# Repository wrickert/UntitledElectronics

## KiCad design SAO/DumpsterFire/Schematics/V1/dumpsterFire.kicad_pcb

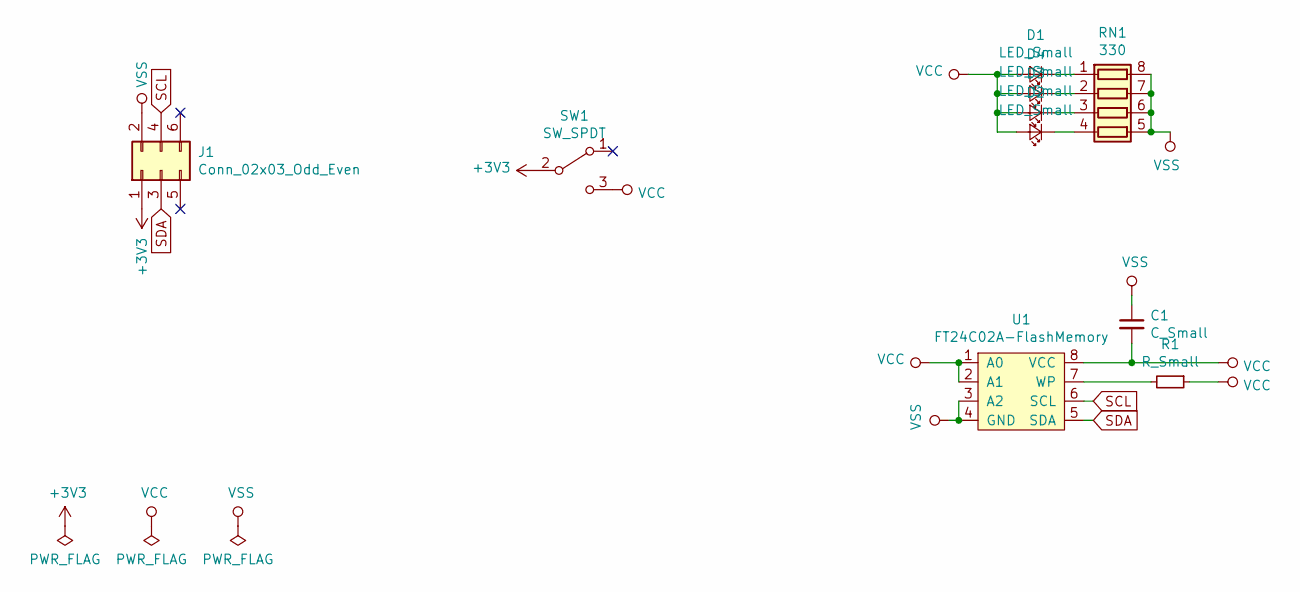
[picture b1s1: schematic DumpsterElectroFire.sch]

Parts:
C1: C_Small; C_0805_2012Metric
D1, D2, D3, D4: LED_Small; LED_0603_1608Metric
J1: Conn_02x03_Odd_Even; PinHeader_2x03_P2.54mm_Vertical_SMD
R1: R_Small; R_0805_2012Metric
RN1: 330; R_Array_Convex_4x0603
SW1: SW_SPDT; SK-3296S_switch
U1: FT24C02A-FlashMemory; SOP-8_3.9x4.9mm_P1.27mm

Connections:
+3V3: J1.1, SW1.2 (B)
unnamed: D1.1 (K), RN1.1 (R1.1)
unnamed: D2.1 (K), RN1.4 (R4.1)
unnamed: D3.1 (K), RN1.3 (R3.1)
unnamed: D4.1 (K), RN1.2 (R2.1)
unnamed: R1.2, U1.7 (WP)
SCL: J1.4, U1.6 (SCL)
SDA: J1.3, U1.5 (SDA)
VCC: C1.2, D1.2 (A), D2.2 (A), D3.2 (A), D4.2 (A), R1.1, SW1.3 (C), U1.1 (A0), U1.2 (A1), U1.8 (VCC)
VSS: C1.1, J1.2, RN1.5 (R4.2), RN1.6 (R3.2), RN1.7 (R2.2), RN1.8 (R1.2), U1.3 (A2), U1.4 (GND)

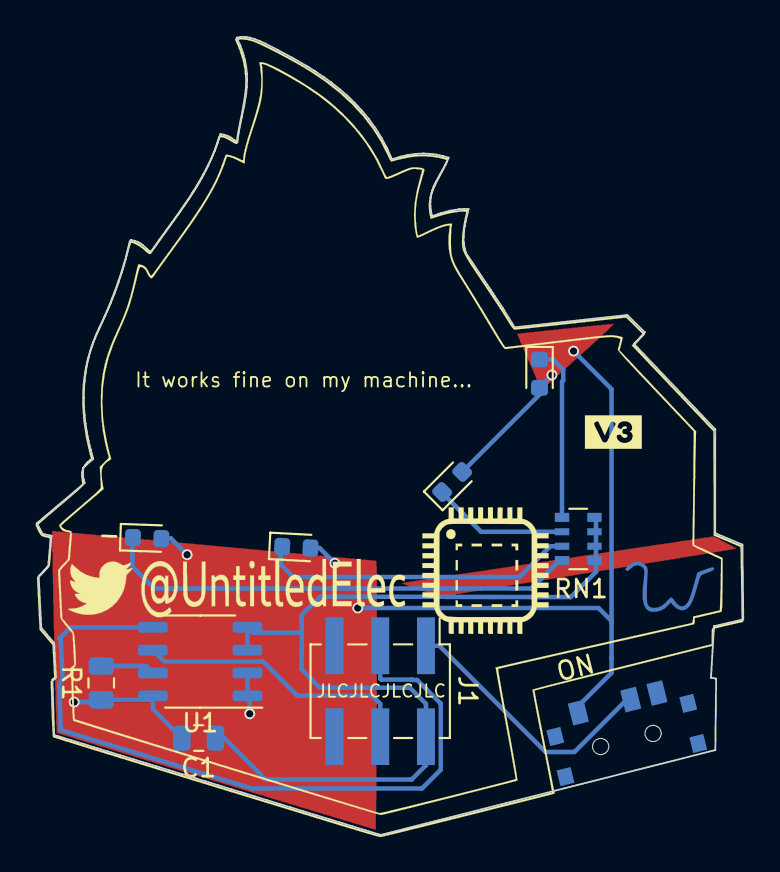
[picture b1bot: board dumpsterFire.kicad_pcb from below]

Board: 2 copper layers, 39.2 x 44.3 mm, 15 parts (14 on the bottom side), 10 nets.

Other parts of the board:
Ref**: Val**; dumpsterFireMiddle
Ref**#2: Val**; W
Ref**#3: Val**; TwitterSmaller
Ref**#4: Val**; JustChip
svg2mod: G***; svg2mod

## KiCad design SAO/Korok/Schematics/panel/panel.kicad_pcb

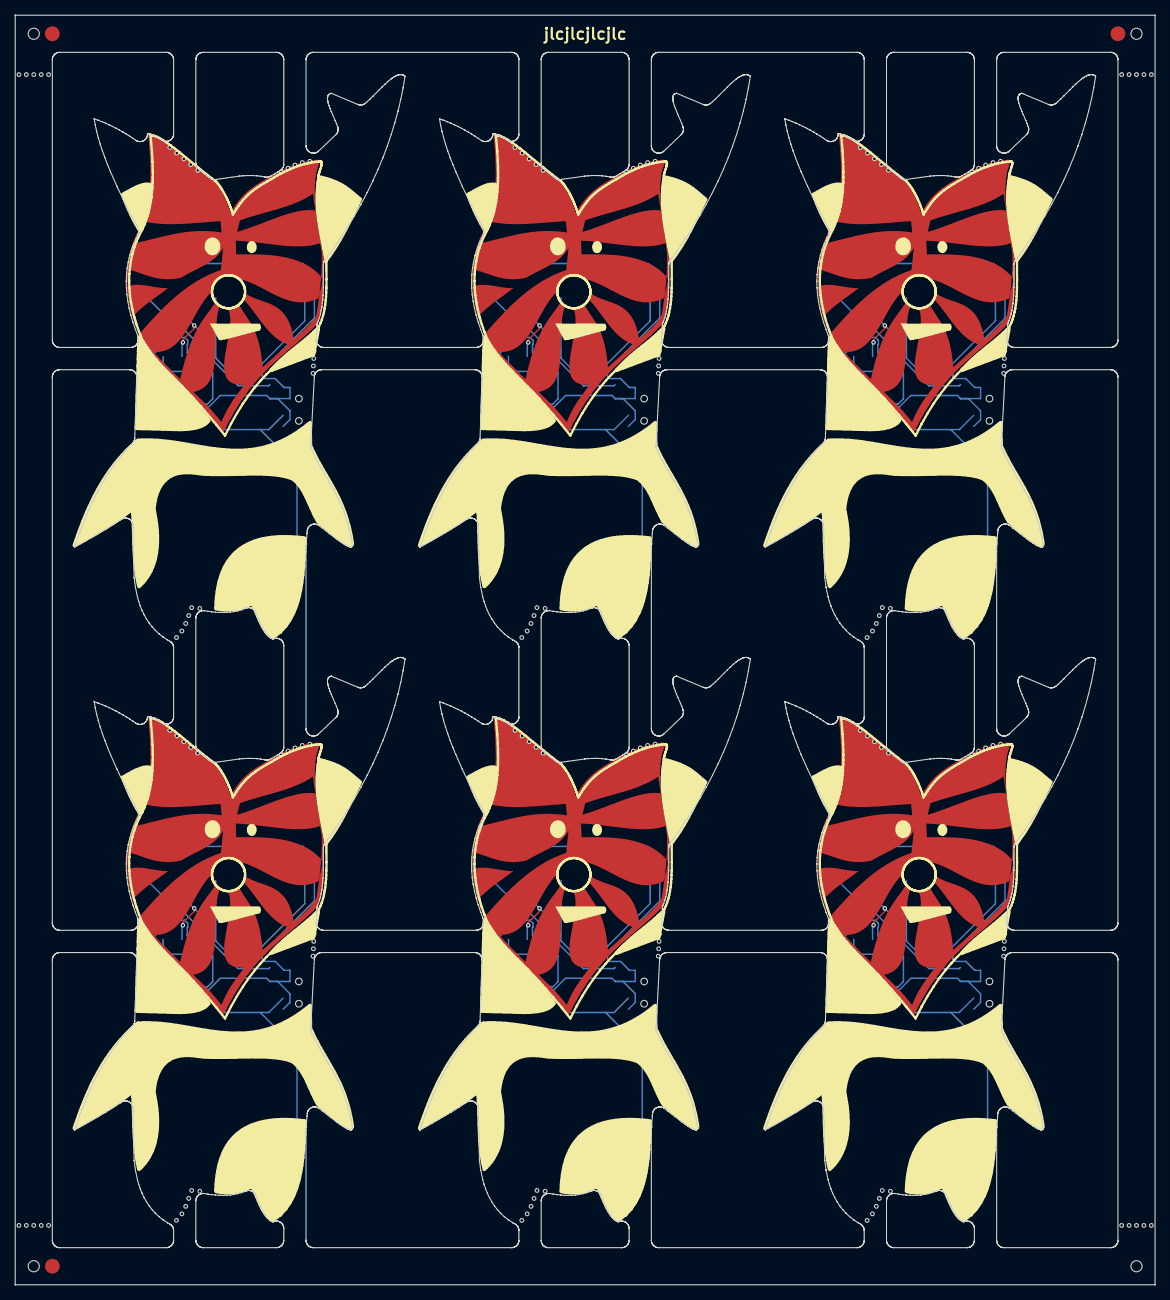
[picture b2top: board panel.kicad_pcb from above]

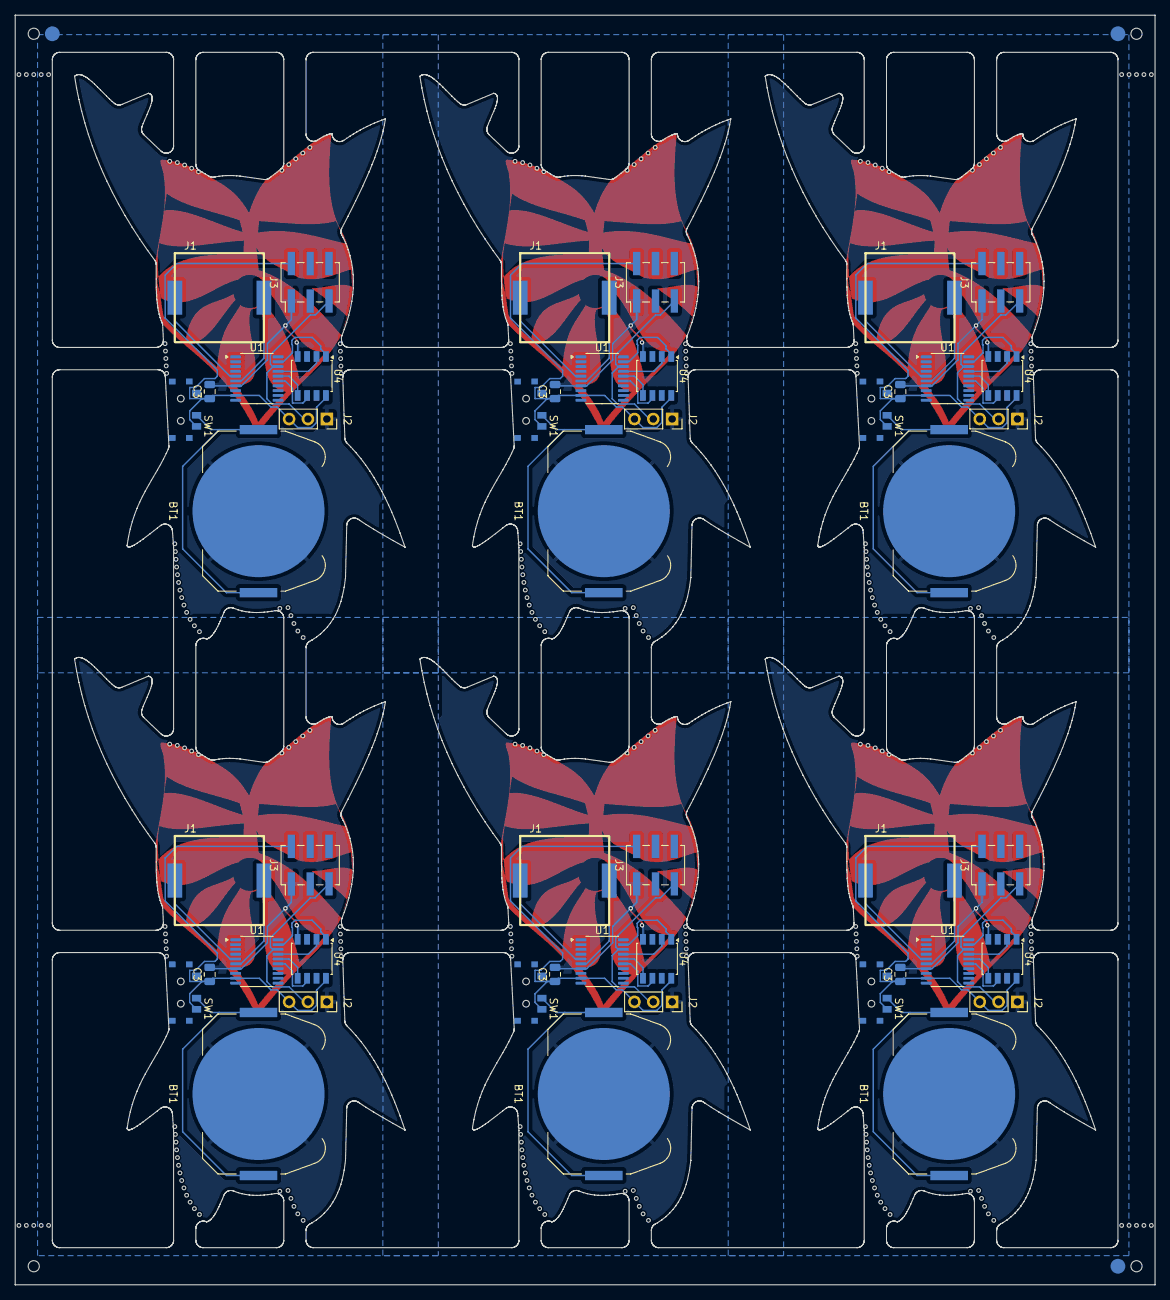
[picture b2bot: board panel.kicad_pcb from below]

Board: 2 copper layers, 153.6 x 171.1 mm, 312 parts (51 on the bottom side), 60 nets.

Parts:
BT1, BT1#2, BT1#3, BT1#4, BT1#5, BT1#6: Battery_Cell; BatteryHolder_Keystone_3034_1x20mm
C3, C3#2, C3#3, C3#4, C3#5, C3#6: 100n; C_0805_2012Metric
J1, J1#2, J1#3, J1#4, J1#5, J1#6: Speaker; Fuet-1230
J2, J2#2, J2#3, J2#4, J2#5, J2#6: Debug; PinSocket_1x03_P2.54mm_Vertical
J3, J3#2, J3#3, J3#4, J3#5, J3#6: Conn_02x03_Odd_Even; PinHeader_2x03_P2.54mm_Vertical_SMD
KiKit_FID_B_1, KiKit_FID_B_2, KiKit_FID_B_3: Fiducial
KiKit_FID_T_1, KiKit_FID_T_2, KiKit_FID_T_3: Fiducial
KiKit_MB_1_1, KiKit_MB_1_2, KiKit_MB_1_3, KiKit_MB_1_4, KiKit_MB_1_5, KiKit_MB_2_1, KiKit_MB_2_2, KiKit_MB_2_3, KiKit_MB_2_4, KiKit_MB_2_5, KiKit_MB_3_1, KiKit_MB_3_2, KiKit_MB_3_3, KiKit_MB_3_4, KiKit_MB_3_5, KiKit_MB_4_1, KiKit_MB_4_2, KiKit_MB_4_3, KiKit_MB_4_4, KiKit_MB_4_5, KiKit_MB_5_1, KiKit_MB_5_2, KiKit_MB_5_3, KiKit_MB_5_4, KiKit_MB_5_5, KiKit_MB_5_6, KiKit_MB_6_1, KiKit_MB_6_2, KiKit_MB_6_3, KiKit_MB_6_4, KiKit_MB_6_5, KiKit_MB_6_6, KiKit_MB_6_7, KiKit_MB_6_8, KiKit_MB_6_9, KiKit_MB_6_10, KiKit_MB_6_11, KiKit_MB_6_12, KiKit_MB_6_13, KiKit_MB_7_1, KiKit_MB_7_2, KiKit_MB_7_3, KiKit_MB_7_4, KiKit_MB_7_5, KiKit_MB_8_1, KiKit_MB_8_2, KiKit_MB_8_3, KiKit_MB_8_4, KiKit_MB_8_5, KiKit_MB_9_1, KiKit_MB_9_2, KiKit_MB_9_3, KiKit_MB_9_4, KiKit_MB_9_5, KiKit_MB_10_1, KiKit_MB_10_2, KiKit_MB_10_3, KiKit_MB_10_4, KiKit_MB_10_5, KiKit_MB_11_1, KiKit_MB_11_2, KiKit_MB_11_3, KiKit_MB_11_4, KiKit_MB_11_5, KiKit_MB_11_6, KiKit_MB_12_1, KiKit_MB_12_2, KiKit_MB_12_3, KiKit_MB_12_4, KiKit_MB_12_5, KiKit_MB_12_6, KiKit_MB_12_7, KiKit_MB_12_8, KiKit_MB_12_9, KiKit_MB_12_10, KiKit_MB_12_11, KiKit_MB_12_12, KiKit_MB_12_13, KiKit_MB_13_1, KiKit_MB_13_2, KiKit_MB_13_3, KiKit_MB_13_4, KiKit_MB_13_5, KiKit_MB_14_1, KiKit_MB_14_2, KiKit_MB_14_3, KiKit_MB_14_4, KiKit_MB_14_5, KiKit_MB_15_1, KiKit_MB_15_2, KiKit_MB_15_3, KiKit_MB_15_4, KiKit_MB_15_5, KiKit_MB_16_1, KiKit_MB_16_2, KiKit_MB_16_3, KiKit_MB_16_4, KiKit_MB_16_5, KiKit_MB_17_1, KiKit_MB_17_2, KiKit_MB_17_3, KiKit_MB_17_4, KiKit_MB_17_5, KiKit_MB_17_6, KiKit_MB_18_1, KiKit_MB_18_2, KiKit_MB_18_3, KiKit_MB_18_4, KiKit_MB_18_5, KiKit_MB_18_6, KiKit_MB_18_7, KiKit_MB_18_8, KiKit_MB_18_9, KiKit_MB_18_10, KiKit_MB_18_11, KiKit_MB_18_12, KiKit_MB_18_13, KiKit_MB_19_1, KiKit_MB_19_2, KiKit_MB_19_3, KiKit_MB_19_4, KiKit_MB_19_5, KiKit_MB_20_1, KiKit_MB_20_2, KiKit_MB_20_3, KiKit_MB_20_4, KiKit_MB_20_5, KiKit_MB_21_1, KiKit_MB_21_2, KiKit_MB_21_3, KiKit_MB_21_4, KiKit_MB_21_5, KiKit_MB_22_1, KiKit_MB_22_2, KiKit_MB_22_3, KiKit_MB_22_4, KiKit_MB_22_5, KiKit_MB_23_1, KiKit_MB_23_2, KiKit_MB_23_3, KiKit_MB_23_4, KiKit_MB_23_5, KiKit_MB_23_6, KiKit_MB_24_1, KiKit_MB_24_2, KiKit_MB_24_3, KiKit_MB_24_4, KiKit_MB_24_5, KiKit_MB_24_6, KiKit_MB_24_7, KiKit_MB_24_8, KiKit_MB_24_9, KiKit_MB_24_10, KiKit_MB_24_11, KiKit_MB_24_12, KiKit_MB_24_13, KiKit_MB_25_1, KiKit_MB_25_2, KiKit_MB_25_3, KiKit_MB_25_4, KiKit_MB_25_5, KiKit_MB_26_1, KiKit_MB_26_2, KiKit_MB_26_3, KiKit_MB_26_4, KiKit_MB_26_5, KiKit_MB_27_1, KiKit_MB_27_2, KiKit_MB_27_3, KiKit_MB_27_4, KiKit_MB_27_5, KiKit_MB_28_1, KiKit_MB_28_2, KiKit_MB_28_3, KiKit_MB_28_4, KiKit_MB_28_5, KiKit_MB_29_1, KiKit_MB_29_2, KiKit_MB_29_3, KiKit_MB_29_4, KiKit_MB_29_5, KiKit_MB_29_6, KiKit_MB_30_1, KiKit_MB_30_2, KiKit_MB_30_3, KiKit_MB_30_4, KiKit_MB_30_5, KiKit_MB_30_6, KiKit_MB_30_7, KiKit_MB_30_8, KiKit_MB_30_9, KiKit_MB_30_10, KiKit_MB_30_11, KiKit_MB_30_12, KiKit_MB_30_13, KiKit_MB_31_1, KiKit_MB_31_2, KiKit_MB_31_3, KiKit_MB_31_4, KiKit_MB_31_5, KiKit_MB_32_1, KiKit_MB_32_2, KiKit_MB_32_3, KiKit_MB_32_4, KiKit_MB_32_5, KiKit_MB_33_1, KiKit_MB_33_2, KiKit_MB_33_3, KiKit_MB_33_4, KiKit_MB_33_5, KiKit_MB_34_1, KiKit_MB_34_2, KiKit_MB_34_3, KiKit_MB_34_4, KiKit_MB_34_5, KiKit_MB_35_1, KiKit_MB_35_2, KiKit_MB_35_3, KiKit_MB_35_4, KiKit_MB_35_5, KiKit_MB_35_6, KiKit_MB_36_1, KiKit_MB_36_2, KiKit_MB_36_3, KiKit_MB_36_4, KiKit_MB_36_5, KiKit_MB_36_6, KiKit_MB_36_7, KiKit_MB_36_8, KiKit_MB_36_9, KiKit_MB_36_10, KiKit_MB_36_11, KiKit_MB_36_12, KiKit_MB_36_13, KiKit_MB_37_2, KiKit_MB_37_3, KiKit_MB_37_4, KiKit_MB_37_5, KiKit_MB_37_6, KiKit_MB_38_2, KiKit_MB_38_3, KiKit_MB_38_4, KiKit_MB_38_5, KiKit_MB_38_6, KiKit_MB_39_2, KiKit_MB_39_3, KiKit_MB_39_4, KiKit_MB_39_5, KiKit_MB_39_6, KiKit_MB_40_2, KiKit_MB_40_3, KiKit_MB_40_4, KiKit_MB_40_5, KiKit_MB_40_6: NPTH
KiKit_TO_1, KiKit_TO_2, KiKit_TO_3, KiKit_TO_4: NPTH
SW1, SW1#2, SW1#3, SW1#4, SW1#5, SW1#6: SW_SPDT; SK-3296S_switch
U1, U1#2, U1#3, U1#4, U1#5, U1#6: CH32V006; TSSOP-20_4.4x6.5mm_P0.65mm
U4, U4#2, U4#3, U4#4, U4#5, U4#6: W25Q16JVSS; SSOP-8_3.95x5.21x3.27mm_P1.27mm

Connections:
Board_0-+3V3: C3#5.1, J2#5.3, J3#3.2, SW1#5.1 (A), U1#3.9 (VDD), U4.8 (VCC)
Board_0-GND: BT1#5.2 (-), C3#5.2, J2#5.1, J3#3.1, U1#3.7 (VSS), U4.4 (GND)
Board_0-Net-(BT1-+): BT1#5.1 (+), SW1#5.2 (B)
Board_0-PA1: J1#2.1, U1#3.5 (PA1/T1/T2/OPN0/XI/A1)
Board_0-PA2: J1#2.2, U1#3.6 (PA2/T1/T2/U2TX_/OPP0/XO/A0)
Board_0-PC5: U1#3.15 (PC5/T1C2_/T1/T2/TX_/SCK), U4.6 (CLK)
Board_0-PC6: U1#3.16 (PC6/T1C3_/T1/RX_/MOSI), U4.5 (DI(IO0))
Board_0-PC7: U1#3.17 (PC7/T1C4_/T1/T2/MISO), U4.2 (DO(IO1))
Board_0-PD2: U1#3.19 (PD2/T1/T2/U2TX_/A3), U4.1 (~CS)
Board_0-SWIO: J2#5.2, J3#3.5, U1#3.18 (PD1/SWIO/T1/SCL_/RX_/OPP3)
Board_1-+3V3: C3#4.1, J2#2.3, J3#5.2, SW1#2.1 (A), U1#4.9 (VDD), U4#2.8 (VCC)
Board_1-GND: BT1#6.2 (-), C3#4.2, J2#2.1, J3#5.1, U1#4.7 (VSS), U4#2.4 (GND)
Board_1-Net-(BT1-+): BT1#6.1 (+), SW1#2.2 (B)
Board_1-PA1: J1#4.1, U1#4.5 (PA1/T1/T2/OPN0/XI/A1)
Board_1-PA2: J1#4.2, U1#4.6 (PA2/T1/T2/U2TX_/OPP0/XO/A0)
Board_1-PC5: U1#4.15 (PC5/T1C2_/T1/T2/TX_/SCK), U4#2.6 (CLK)
Board_1-PC6: U1#4.16 (PC6/T1C3_/T1/RX_/MOSI), U4#2.5 (DI(IO0))
Board_1-PC7: U1#4.17 (PC7/T1C4_/T1/T2/MISO), U4#2.2 (DO(IO1))
Board_1-PD2: U1#4.19 (PD2/T1/T2/U2TX_/A3), U4#2.1 (~CS)
Board_1-SWIO: J2#2.2, J3#5.5, U1#4.18 (PD1/SWIO/T1/SCL_/RX_/OPP3)
Board_2-+3V3: C3#6.1, J2.3, J3#4.2, SW1#4.1 (A), U1.9 (VDD), U4#4.8 (VCC)
Board_2-GND: BT1#4.2 (-), C3#6.2, J2.1, J3#4.1, U1.7 (VSS), U4#4.4 (GND)
Board_2-Net-(BT1-+): BT1#4.1 (+), SW1#4.2 (B)
Board_2-PA1: J1#6.1, U1.5 (PA1/T1/T2/OPN0/XI/A1)
Board_2-PA2: J1#6.2, U1.6 (PA2/T1/T2/U2TX_/OPP0/XO/A0)
Board_2-PC5: U1.15 (PC5/T1C2_/T1/T2/TX_/SCK), U4#4.6 (CLK)
Board_2-PC6: U1.16 (PC6/T1C3_/T1/RX_/MOSI), U4#4.5 (DI(IO0))
Board_2-PC7: U1.17 (PC7/T1C4_/T1/T2/MISO), U4#4.2 (DO(IO1))
Board_2-PD2: U1.19 (PD2/T1/T2/U2TX_/A3), U4#4.1 (~CS)
Board_2-SWIO: J2.2, J3#4.5, U1.18 (PD1/SWIO/T1/SCL_/RX_/OPP3)
Board_3-+3V3: C3#3.1, J2#6.3, J3#6.2, SW1#6.1 (A), U1#2.9 (VDD), U4#3.8 (VCC)
Board_3-GND: BT1.2 (-), C3#3.2, J2#6.1, J3#6.1, U1#2.7 (VSS), U4#3.4 (GND)
Board_3-Net-(BT1-+): BT1.1 (+), SW1#6.2 (B)
Board_3-PA1: J1#3.1, U1#2.5 (PA1/T1/T2/OPN0/XI/A1)
Board_3-PA2: J1#3.2, U1#2.6 (PA2/T1/T2/U2TX_/OPP0/XO/A0)
Board_3-PC5: U1#2.15 (PC5/T1C2_/T1/T2/TX_/SCK), U4#3.6 (CLK)
Board_3-PC6: U1#2.16 (PC6/T1C3_/T1/RX_/MOSI), U4#3.5 (DI(IO0))
Board_3-PC7: U1#2.17 (PC7/T1C4_/T1/T2/MISO), U4#3.2 (DO(IO1))
Board_3-PD2: U1#2.19 (PD2/T1/T2/U2TX_/A3), U4#3.1 (~CS)
Board_3-SWIO: J2#6.2, J3#6.5, U1#2.18 (PD1/SWIO/T1/SCL_/RX_/OPP3)
Board_4-+3V3: C3.1, J2#3.3, J3.2, SW1#3.1 (A), U1#6.9 (VDD), U4#5.8 (VCC)
Board_4-GND: BT1#2.2 (-), C3.2, J2#3.1, J3.1, U1#6.7 (VSS), U4#5.4 (GND)
Board_4-Net-(BT1-+): BT1#2.1 (+), SW1#3.2 (B)
Board_4-PA1: J1.1, U1#6.5 (PA1/T1/T2/OPN0/XI/A1)
Board_4-PA2: J1.2, U1#6.6 (PA2/T1/T2/U2TX_/OPP0/XO/A0)
Board_4-PC5: U1#6.15 (PC5/T1C2_/T1/T2/TX_/SCK), U4#5.6 (CLK)
Board_4-PC6: U1#6.16 (PC6/T1C3_/T1/RX_/MOSI), U4#5.5 (DI(IO0))
Board_4-PC7: U1#6.17 (PC7/T1C4_/T1/T2/MISO), U4#5.2 (DO(IO1))
Board_4-PD2: U1#6.19 (PD2/T1/T2/U2TX_/A3), U4#5.1 (~CS)
Board_4-SWIO: J2#3.2, J3.5, U1#6.18 (PD1/SWIO/T1/SCL_/RX_/OPP3)
Board_5-+3V3: C3#2.1, J2#4.3, J3#2.2, SW1.1 (A), U1#5.9 (VDD), U4#6.8 (VCC)
Board_5-GND: BT1#3.2 (-), C3#2.2, J2#4.1, J3#2.1, U1#5.7 (VSS), U4#6.4 (GND)
Board_5-Net-(BT1-+): BT1#3.1 (+), SW1.2 (B)
Board_5-PA1: J1#5.1, U1#5.5 (PA1/T1/T2/OPN0/XI/A1)
Board_5-PA2: J1#5.2, U1#5.6 (PA2/T1/T2/U2TX_/OPP0/XO/A0)
Board_5-PC5: U1#5.15 (PC5/T1C2_/T1/T2/TX_/SCK), U4#6.6 (CLK)
Board_5-PC6: U1#5.16 (PC6/T1C3_/T1/RX_/MOSI), U4#6.5 (DI(IO0))
Board_5-PC7: U1#5.17 (PC7/T1C4_/T1/T2/MISO), U4#6.2 (DO(IO1))
Board_5-PD2: U1#5.19 (PD2/T1/T2/U2TX_/A3), U4#6.1 (~CS)
Board_5-SWIO: J2#4.2, J3#2.5, U1#5.18 (PD1/SWIO/T1/SCL_/RX_/OPP3)

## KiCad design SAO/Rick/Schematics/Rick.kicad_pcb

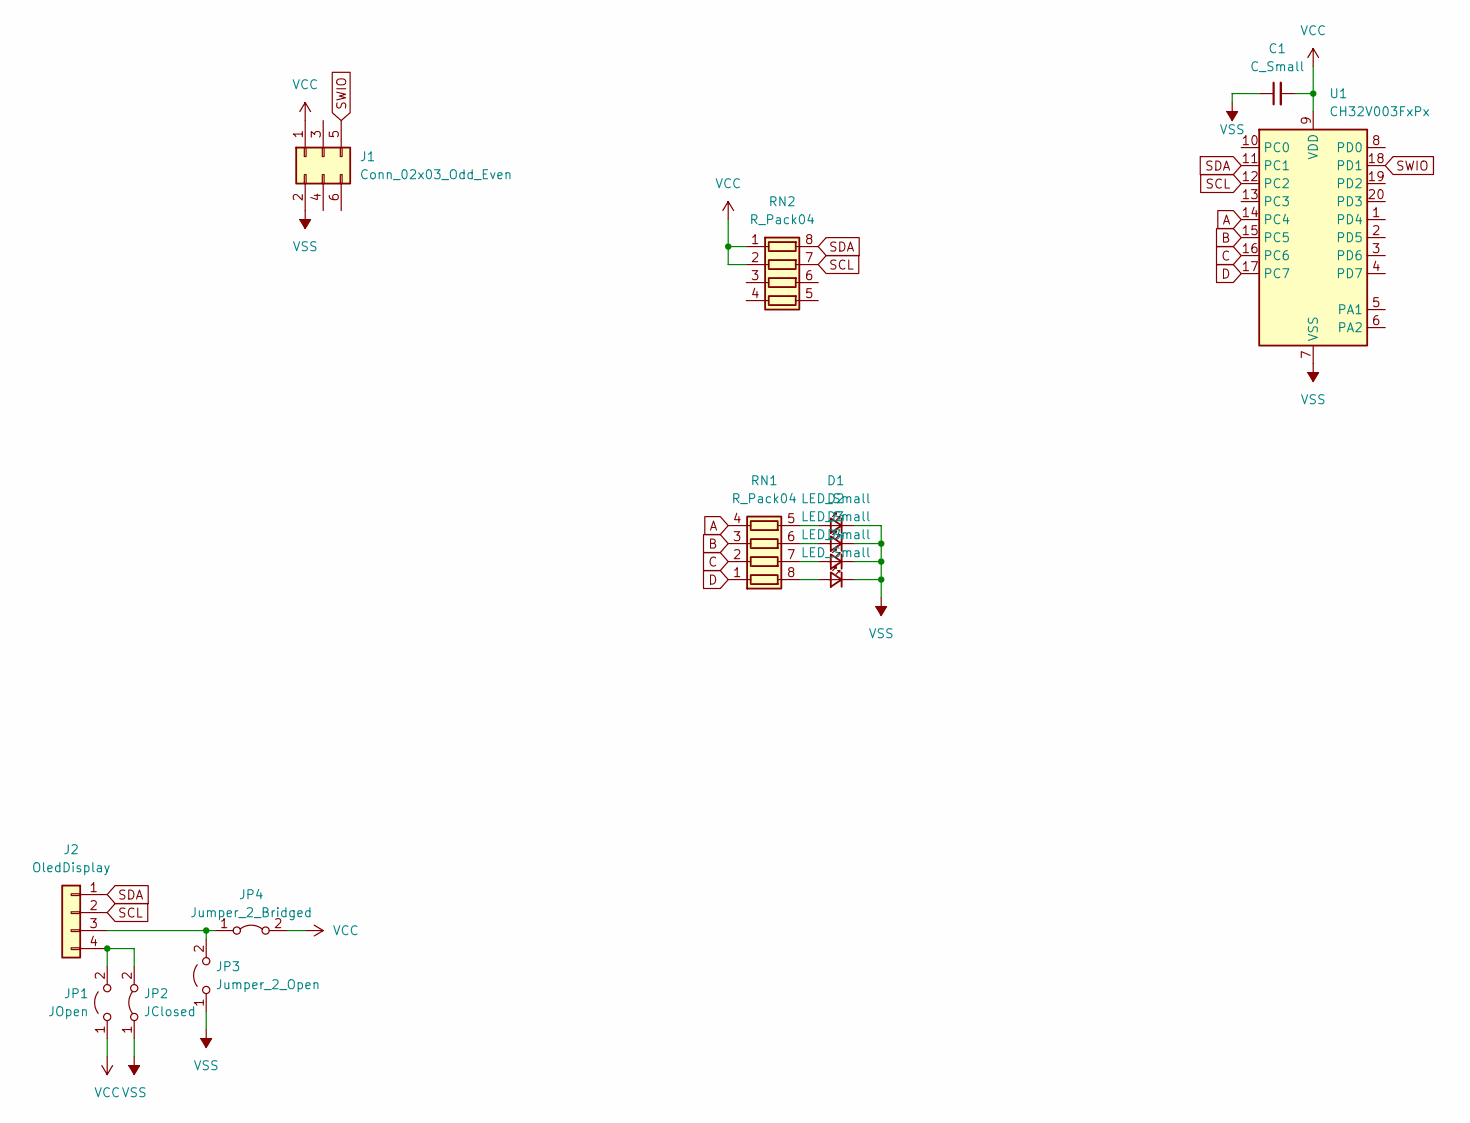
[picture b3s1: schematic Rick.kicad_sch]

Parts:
C1: C_Small; C_0805_2012Metric
D1, D2, D3, D4: LED_Small; 156120VS75000-ReverseCircle
J1: Conn_02x03_Odd_Even; PinHeader_2x03_P2.54mm_Vertical_SMD
J2: OledDisplay; PinHeader_1x04_P2.54mm_Vertical
JP1: JOpen; SolderJumper-2_P1.3mm_Open_TrianglePad1.0x1.5mm
JP2: JClosed; SolderJumper-2_P1.3mm_Bridged_Pad1.0x1.5mm
JP3: Jumper_2_Open; SolderJumper-2_P1.3mm_Open_TrianglePad1.0x1.5mm
JP4: Jumper_2_Bridged; SolderJumper-2_P1.3mm_Bridged_Pad1.0x1.5mm
RN1, RN2: R_Pack04; R_Array_Convex_4x0603
U1: CH32V003FxPx; TSSOP-20_4.4x6.5mm_P0.65mm

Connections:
A: RN1.4 (R4.1), U1.14 (PC4)
B: RN1.3 (R3.1), U1.15 (PC5)
C: RN1.2 (R2.1), U1.16 (PC6)
D: RN1.1 (R1.1), U1.17 (PC7)
unnamed: D1.2 (A), RN1.5 (R4.2)
unnamed: D2.2 (A), RN1.6 (R3.2)
unnamed: D3.2 (A), RN1.7 (R2.2)
unnamed: D4.2 (A), RN1.8 (R1.2)
unnamed: J2.3, JP3.2 (B), JP4.1 (A)
unnamed: J2.4, JP1.2 (B), JP2.2 (B)
SCL: J2.2, RN2.7 (R2.2), U1.12 (PC2)
SDA: J2.1, RN2.8 (R1.2), U1.11 (PC1)
SWIO: J1.5, U1.18 (PD1)
VCC: C1.2, J1.1, JP1.1 (A), JP4.2 (B), RN2.1 (R1.1), RN2.2 (R2.1), U1.9 (VDD)
VSS: C1.1, D1.1 (K), D2.1 (K), D3.1 (K), D4.1 (K), J1.2, JP2.1 (A), JP3.1 (A), U1.7 (VSS)

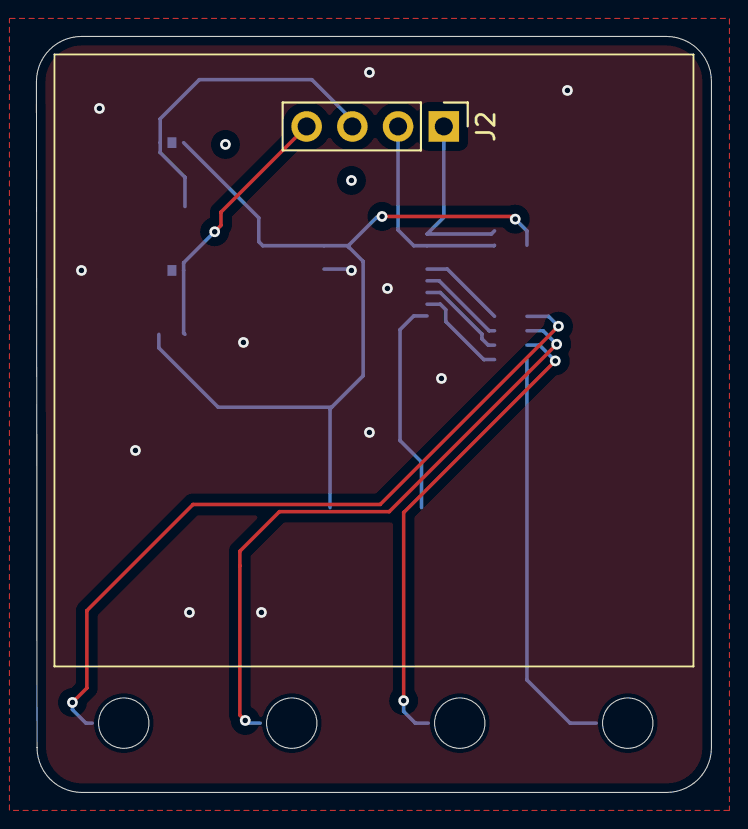
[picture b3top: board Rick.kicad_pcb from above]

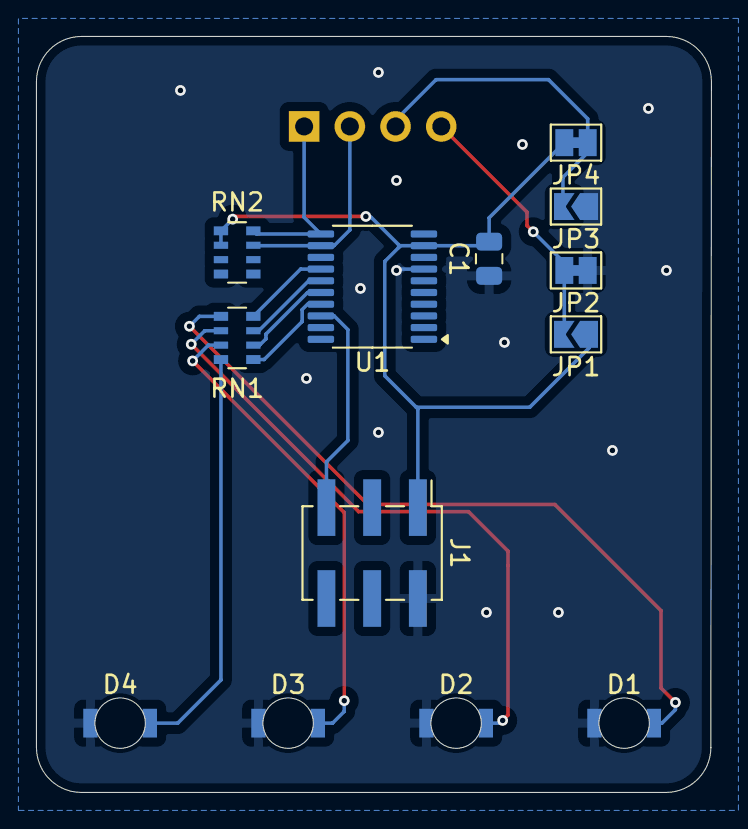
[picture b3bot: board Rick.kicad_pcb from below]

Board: 2 copper layers, 37.5 x 42.0 mm, 14 parts (13 on the bottom side), 15 nets.

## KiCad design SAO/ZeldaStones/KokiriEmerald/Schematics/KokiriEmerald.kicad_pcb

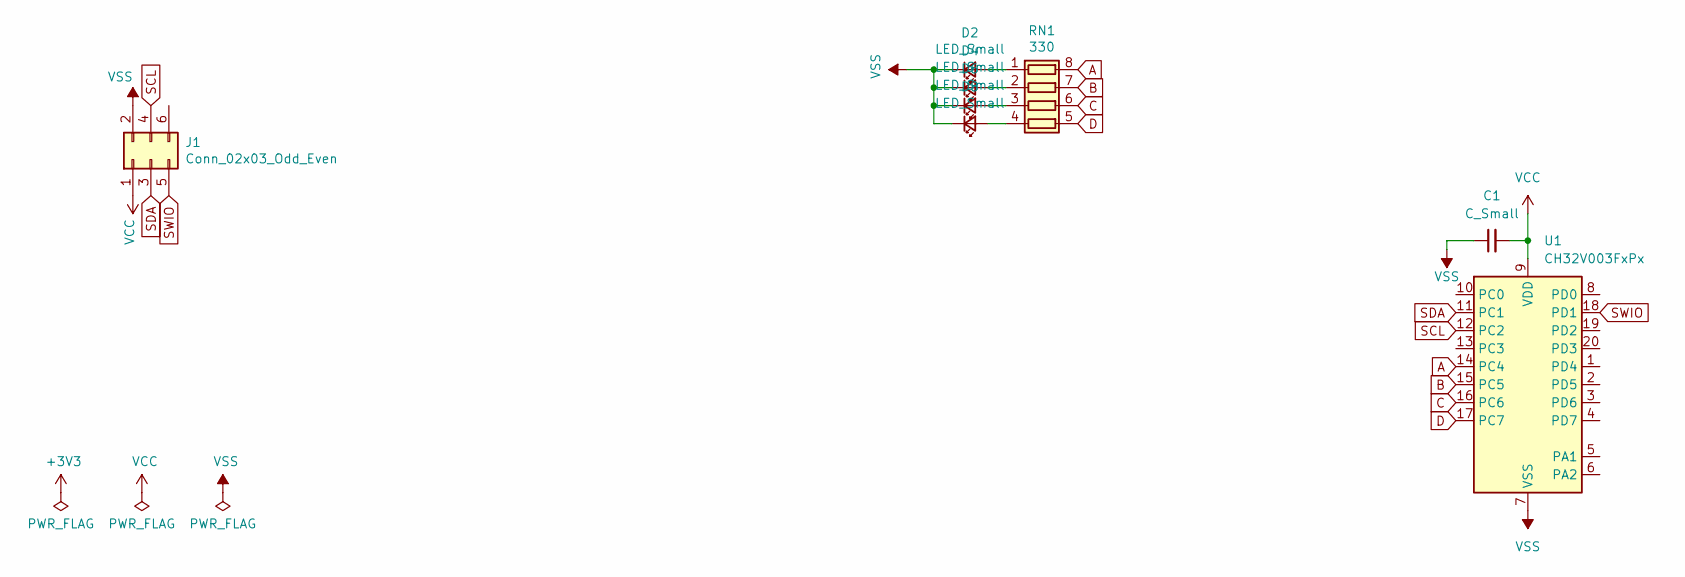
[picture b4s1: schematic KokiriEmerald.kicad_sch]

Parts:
C1: C_Small; C_0805_2012Metric
D2, D4, D6, D8: LED_Small; LED_0603_1608Metric
J1: Conn_02x03_Odd_Even; PinHeader_2x03_P2.54mm_Vertical_SMD
RN1: 330; R_Array_Convex_4x0603
U1: CH32V003FxPx; TSSOP-20_4.4x6.5mm_P0.65mm

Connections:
A: RN1.8 (R1.2), U1.14 (PC4)
B: RN1.7 (R2.2), U1.15 (PC5)
C: RN1.6 (R3.2), U1.16 (PC6)
D: RN1.5 (R4.2), U1.17 (PC7)
unnamed: D2.2 (A), RN1.1 (R1.1)
unnamed: D4.2 (A), RN1.2 (R2.1)
unnamed: D6.2 (A), RN1.3 (R3.1)
unnamed: D8.2 (A), RN1.4 (R4.1)
SCL: J1.4, U1.12 (PC2)
SDA: J1.3, U1.11 (PC1)
SWIO: J1.5, U1.18 (PD1)
VCC: C1.2, J1.1, U1.9 (VDD)
VSS: C1.1, D2.1 (K), D4.1 (K), D6.1 (K), D8.1 (K), J1.2, U1.7 (VSS)

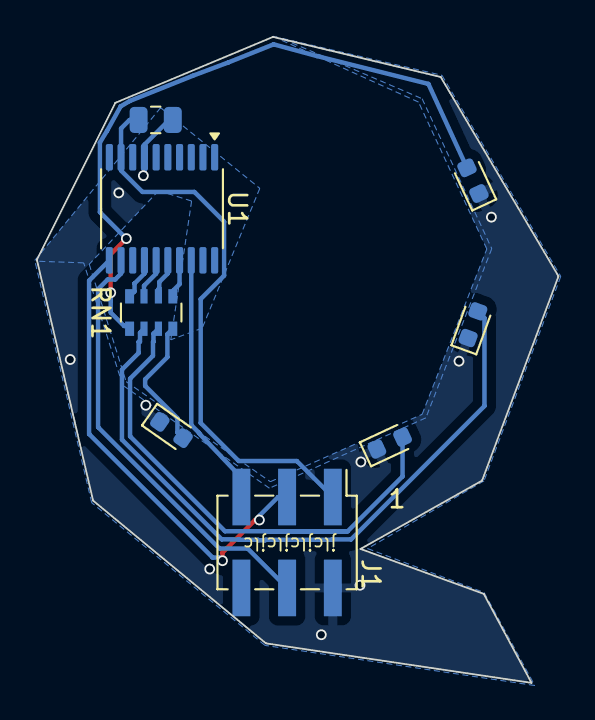
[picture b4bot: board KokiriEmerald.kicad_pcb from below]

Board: 2 copper layers, 29.0 x 35.9 mm, 8 parts (8 on the bottom side), 13 nets.

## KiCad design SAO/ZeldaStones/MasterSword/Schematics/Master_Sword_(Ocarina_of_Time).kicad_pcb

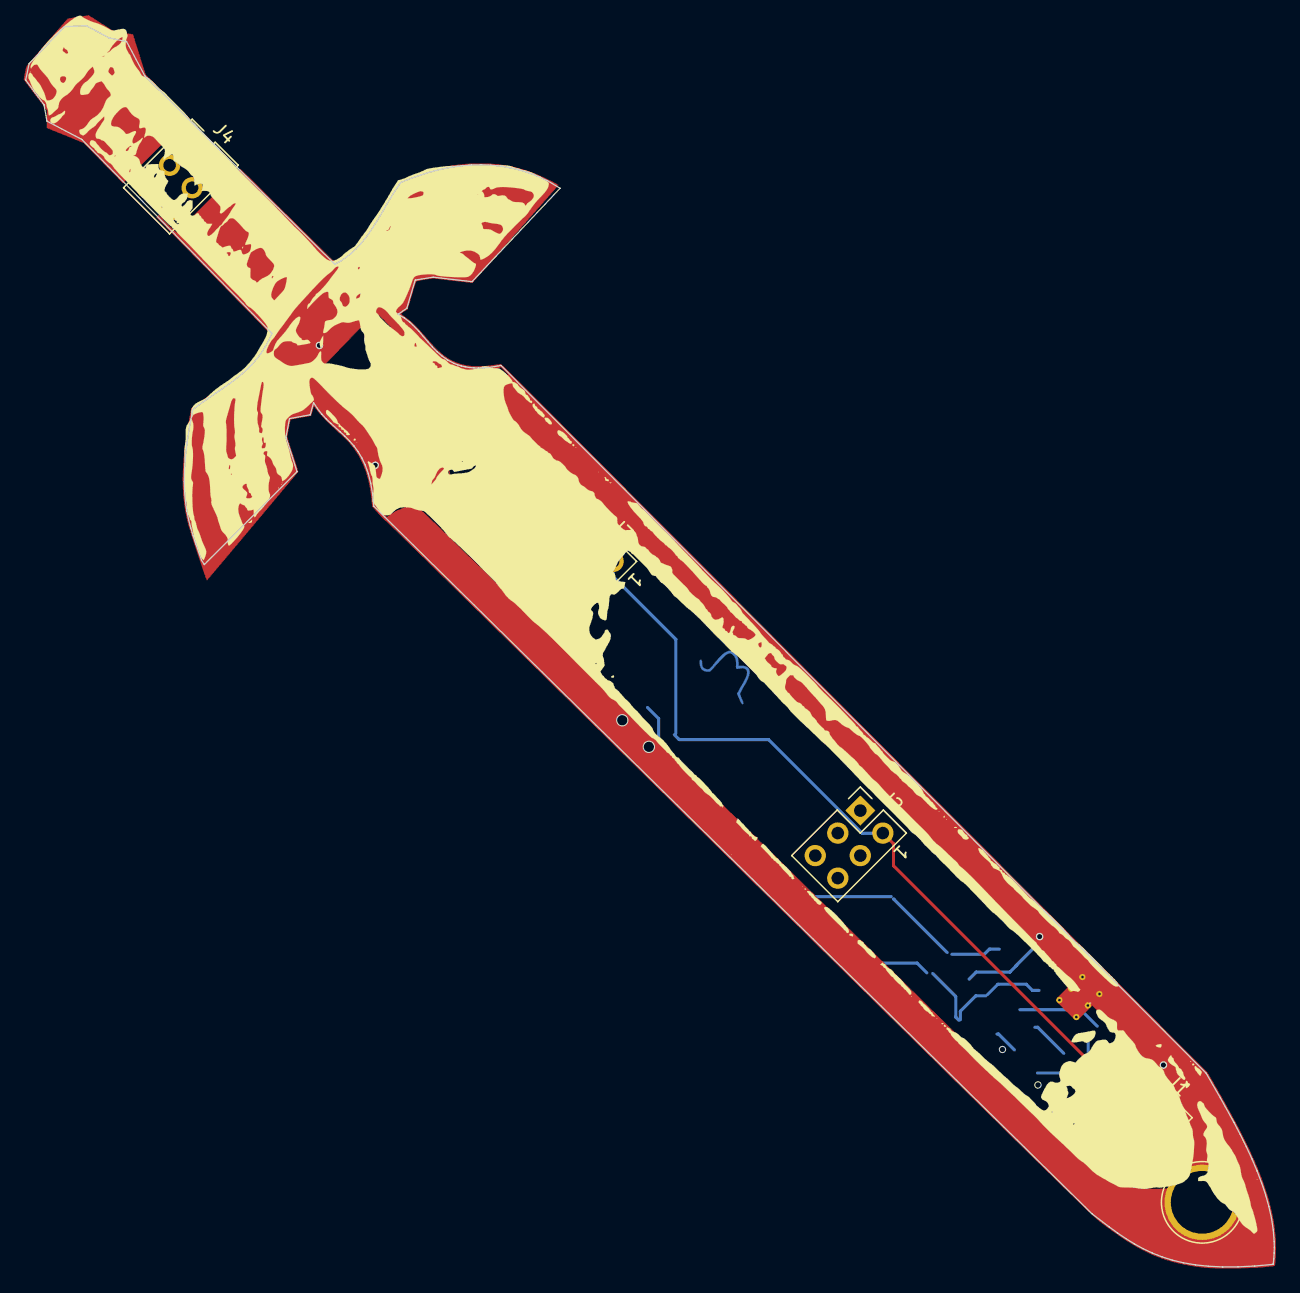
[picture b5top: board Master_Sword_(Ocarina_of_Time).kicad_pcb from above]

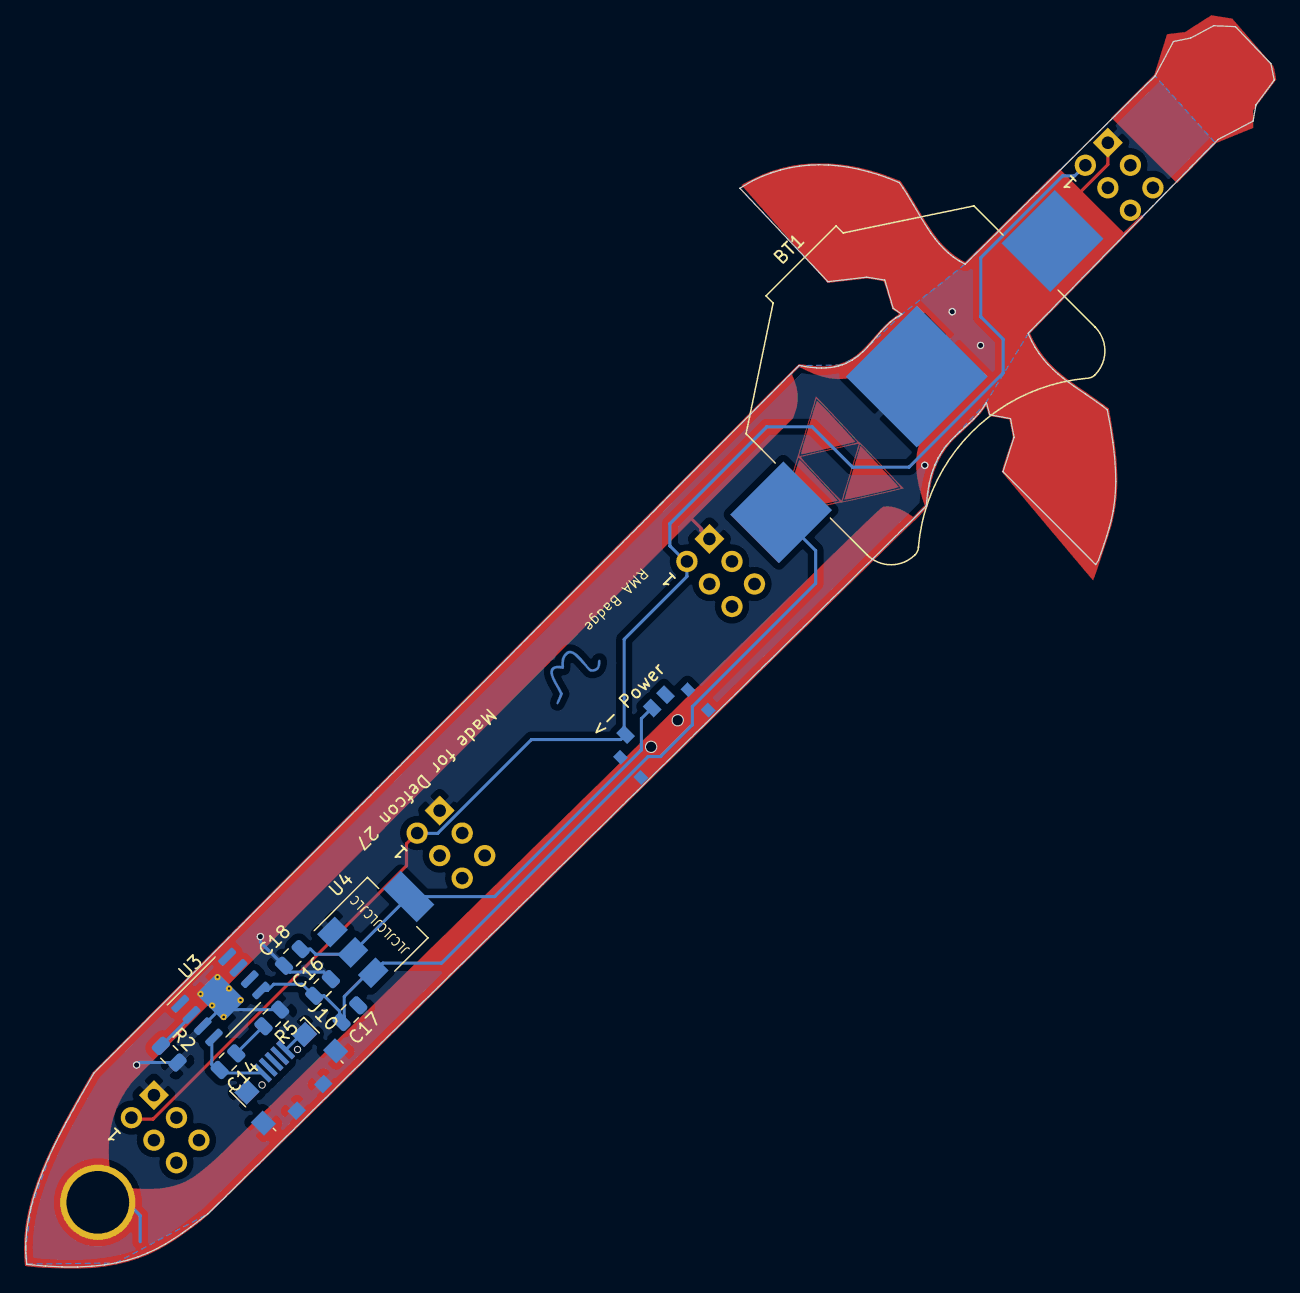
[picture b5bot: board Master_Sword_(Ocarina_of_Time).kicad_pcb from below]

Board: 2 copper layers, 99.6 x 99.0 mm, 16 parts (12 on the bottom side), 7 nets.

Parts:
<- Power: SW_SPDT; SK-3296S_switch
BT1: Battery_Cell; BatteryHolder_Keystone_3008_1x2450
C14, C17: 10uF; C_0805_2012Metric
C16, C18: 1uF; C_0805_2012Metric
J1, J2, J3, J4: Conn_02x03_Odd_Even; PinHeader_2x03_P2.54mm_Vertical
J10: USB_B_Micro; USB_Micro-B_Jing
R2: 1k; R_0805_2012Metric
R5: 1.5; R_0805_2012Metric
Ref**: Val**; W
U3: HX4056; HSOP-8-1EP_3.9x4.9mm_P1.27mm_EP2.41x3.1mm_ThermalVias
U4: TLV1117-33; SOT-223-3_TabPin2

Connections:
+3V3: <- Power.2, C18.1, U4.2
unnamed: C14.1, R5.2
unnamed: C14.2, J10.1, U3.4
unnamed: R2.1, U3.2
VDD: <- Power.3, J1.2, J2.2, J3.2, J4.2
VDDA: BT1.1, C16.1, C17.2, U3.5, U4.3
VSS: BT1.2, C16.2, C17.1, C18.2, J1.1, J2.1, J3.1, J4.1, J10.5, J10.6, R2.2, R5.1, U3.3, U3.9, U4.1
